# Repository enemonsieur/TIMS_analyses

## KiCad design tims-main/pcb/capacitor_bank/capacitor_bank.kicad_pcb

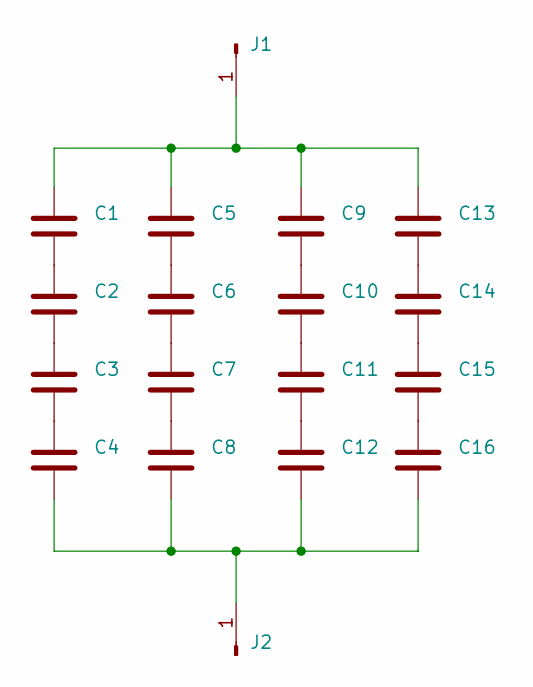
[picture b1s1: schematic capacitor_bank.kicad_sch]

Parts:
C1, C2, C3, C4, C5, C6, C7, C8, C9, C10, C11, C12, C13, C14, C15, C16: C; WIMA MKP10-MULTI
J1, J2: Power_Pad

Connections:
unnamed: C1.2, C2.1
unnamed: C2.2, C3.1
unnamed: C3.2, C4.1
unnamed: C5.2, C6.1
unnamed: C6.2, C7.1
unnamed: C7.2, C8.1
unnamed: C9.2, C10.1
unnamed: C10.2, C11.1
unnamed: C11.2, C12.1
unnamed: C13.2, C14.1
unnamed: C14.2, C15.1
unnamed: C15.2, C16.1
unnamed: C1.1, C5.1, C9.1, C13.1, J1.1
unnamed: C4.2, C8.2, C12.2, C16.2, J2.1

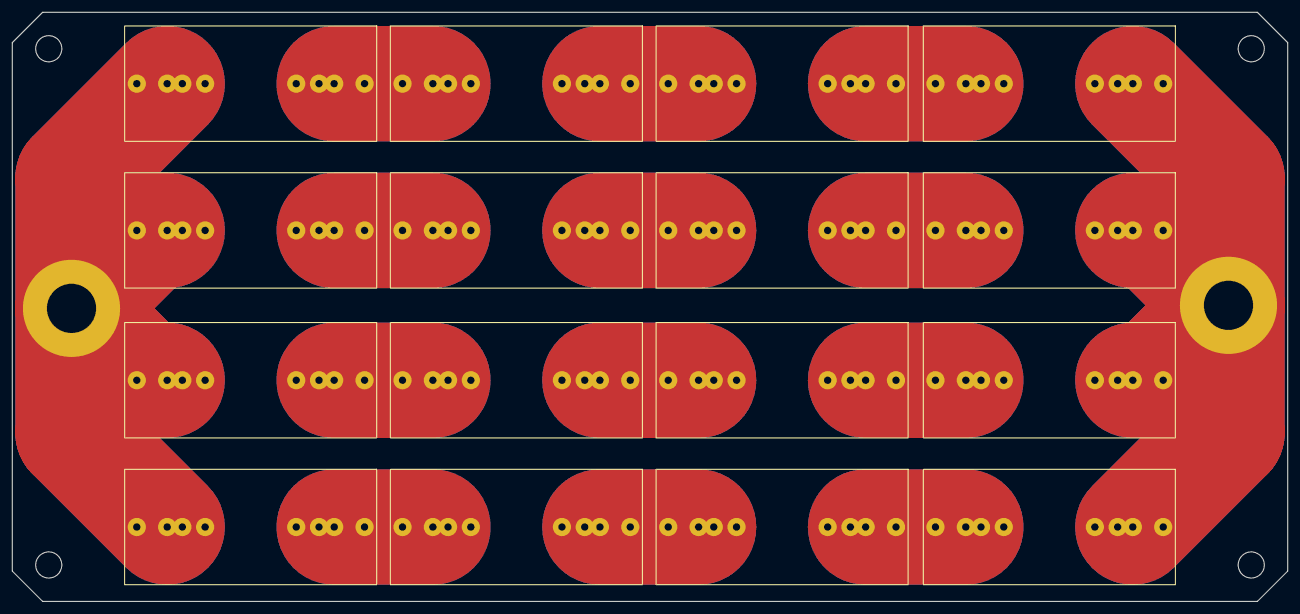
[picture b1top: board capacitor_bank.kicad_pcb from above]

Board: 2 copper layers, 210.0 x 97.0 mm, 18 parts (0 on the bottom side), 14 nets.

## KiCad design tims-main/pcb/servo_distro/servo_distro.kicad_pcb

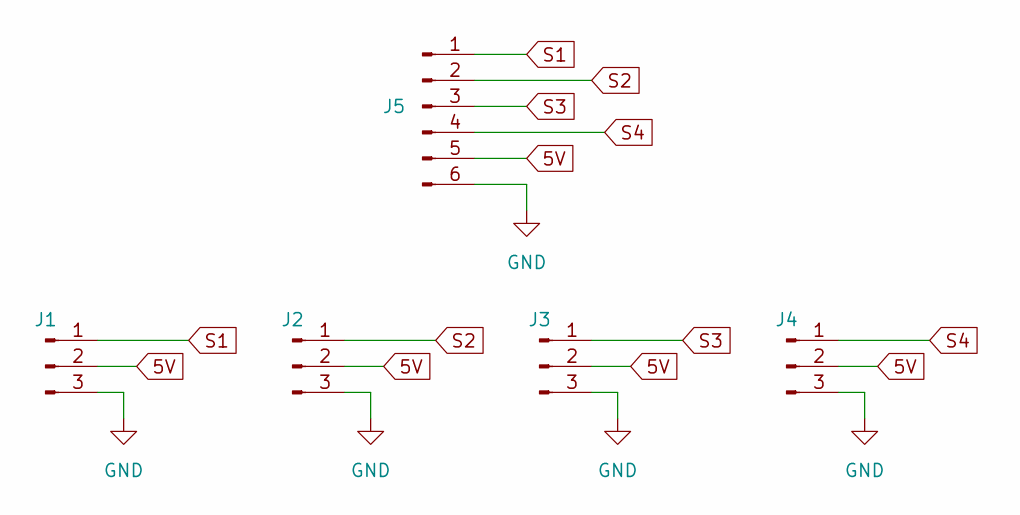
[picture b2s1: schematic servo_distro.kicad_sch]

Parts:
J1, J2, J3, J4: Conn_01x03_Pin; PinHeader_1x03_P2.54mm_Vertical
J5: Conn_01x06_Pin; JST_PH_B6B-PH-K_1x06_P2.00mm_Vertical

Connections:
5V: J1.2, J2.2, J3.2, J4.2, J5.5
GND: J1.3, J2.3, J3.3, J4.3, J5.6
S1: J1.1, J5.1
S2: J2.1, J5.2
S3: J3.1, J5.3
S4: J4.1, J5.4

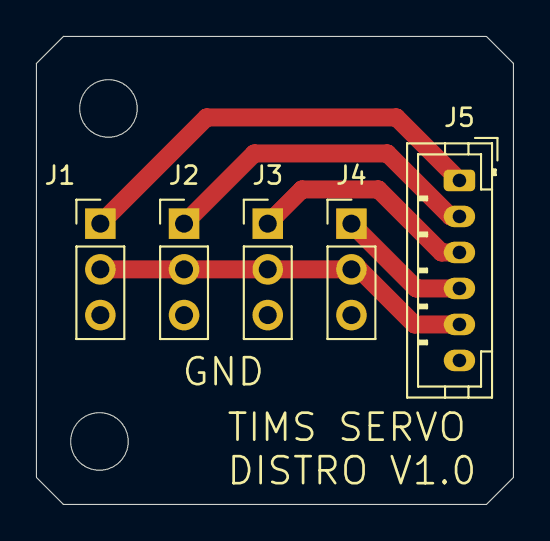
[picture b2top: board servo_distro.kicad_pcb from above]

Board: 2 copper layers, 26.5 x 26.0 mm, 5 parts (0 on the bottom side), 6 nets.
